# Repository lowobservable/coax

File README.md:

# coax

Tools for connecting to real [IBM 3270](https://en.wikipedia.org/wiki/IBM_3270) type terminals.

## Documentation

* [protocol](protocol/protocol.md) - Protocol documentation

## Hardware

* [interface1](interface1) - Legacy interface using obsolete National Semiconductor DP8340 and DP8341
* [interface2](interface2) - Modern interface using a Lattice iCE40 FPGA and STM32 microcontroller

## Software

* [pycoax](pycoax) - Python interface library

## See Also

* [oec](https://github.com/lowobservable/oec) - IBM 3270 terminal controller (a replacement for the IBM 3174)

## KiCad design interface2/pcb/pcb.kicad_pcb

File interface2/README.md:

# interface2

Modern interface using a Lattice iCE40 FPGA and STM32 microcontroller.

## Hardware

You can find a [complete BOM](https://octopart.com/bom-tool/S80JaI18) on Octopart.

You can find the Gerber files for fabricating a PCB in the [fabrication](pcb/fabrication) directory. I have used JLCPCB to make the PCBs.

## FPGA

For now, the FPGA bitstream must be built using Lattice iCEcube2.

```
cd fpga
make
```

Uses FIFO module from [Sylvain Munaut](https://github.com/smunaut).

## Firmware

The firmware currently provides the ability to send commands and receive responses - it is designed to implement a terminal controller, not a terminal.

You will need [PlatformIO](https://platformio.org/) to build and upload the firmware, only Platform IO Core (the CLI) is required.

Before building the firmware, you will need to generate the FPGA bitstream; see the steps above.

To build and upload the firmware using USB DFU:

```
cd firmware
platformio run -t upload
```

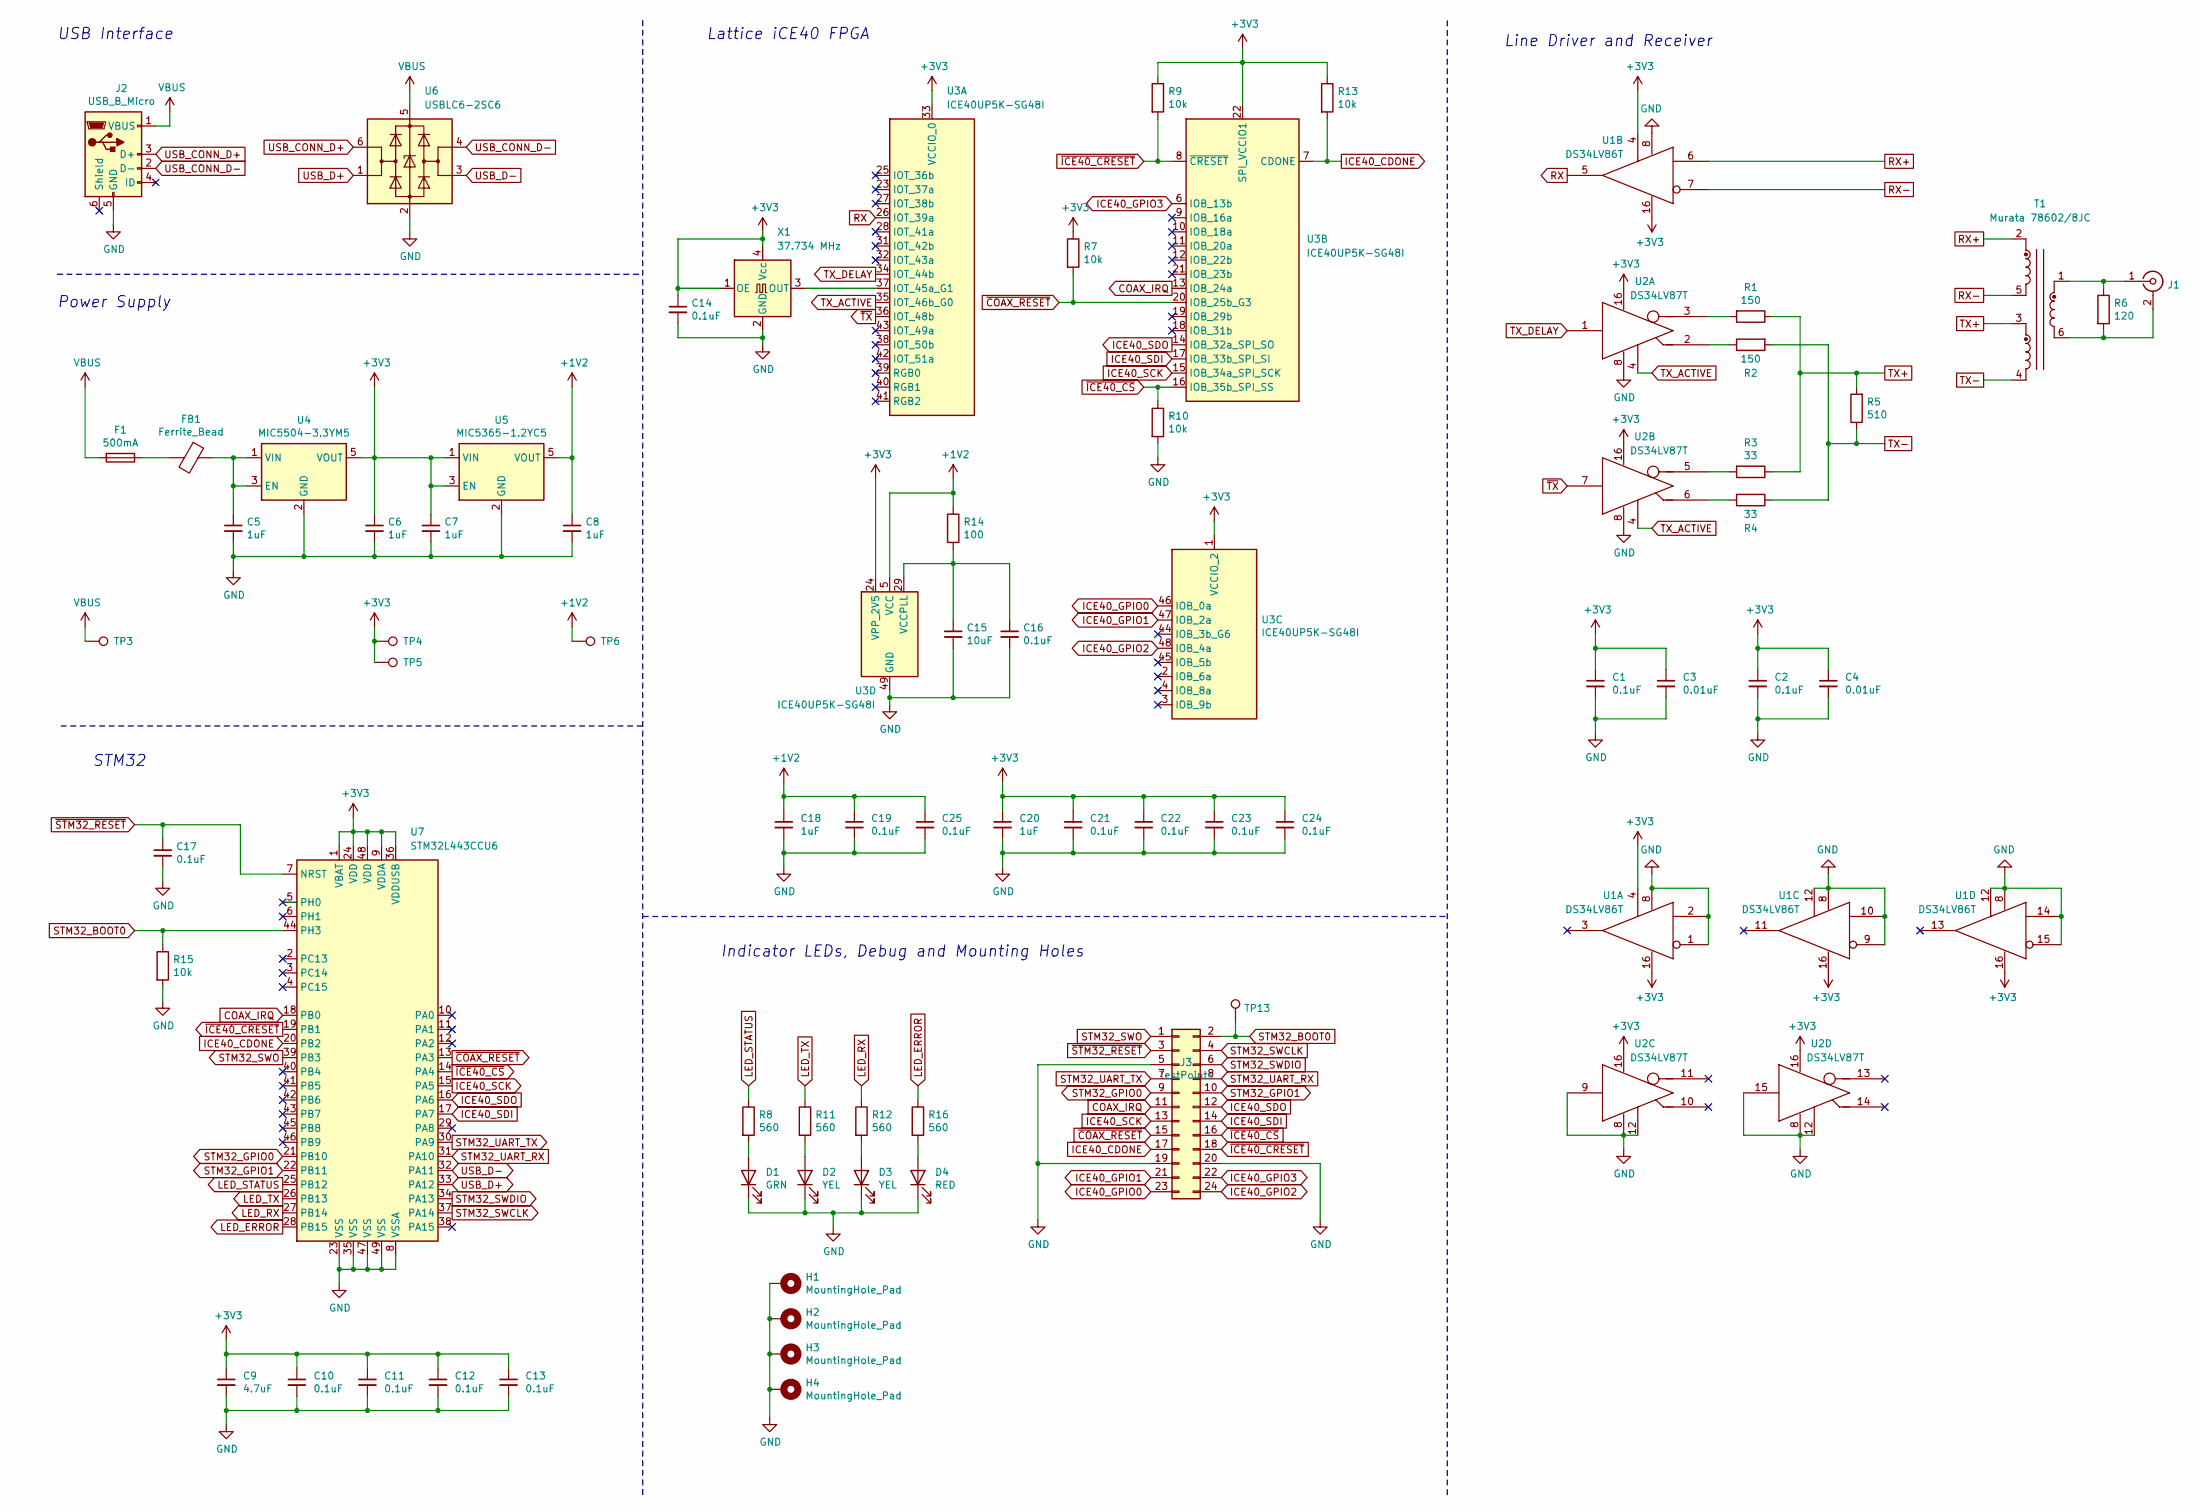
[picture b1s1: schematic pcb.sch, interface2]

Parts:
C1, C2, C10, C11, C12, C13, C14, C16, C17, C19, C21, C22, C23, C24, C25: 0.1uF; C_0603_1608Metric; Part EMK107B7104KA-T
C3, C4: 0.01uF; C_0603_1608Metric; Part HMK107B7103KA-T
C5, C6, C7, C8, C18, C20: 1uF; C_0603_1608Metric; Part EMK107B7105KA-T
C9: 4.7uF; C_0603_1608Metric; Part JMK107BB7475KA-T
C15: 10uF; C_0603_1608Metric; Part JMK107ABJ106KA-T
D1: GRN; LED_0603_1608Metric; Part 150060VS55040
D2, D3: YEL; LED_0603_1608Metric; Part 150060YS55040
D4: RED; LED_0603_1608Metric; Part 150060RS55040
F1: 500mA; Fuse_1206_3216Metric; Part ERB-RG0R50V
FB1: Ferrite_Bead; Fuse_1206_3216Metric; Part CZP2BPTTE101P
H1, H2, H3, H4: MountingHole_Pad; MountingHole_2.7mm_M2.5_ISO7380_Pad
J1: Conn_Coaxial; BNC_Amphenol_B6252HB-NPP3G-50_Horizontal; Part 1-1337543-0
J2: USB_B_Micro; USB_Micro-B_Amphenol_10103594-0001LF_Horizontal; Part 10103594-0001LF
J3: TestPoints; TestPoint_Pad_2x12_D1.0mm
R1, R2: 150; R_0603_1608Metric; Part RCS0603150RFKEA
R3, R4: 33; R_0603_1608Metric; Part RCS060333R0FKEA
R5: 510; R_0603_1608Metric; Part RCS0603510RFKEA
R6: 120; R_0603_1608Metric; Part RCS0603120RFKEA
R7, R9, R10, R13, R15: 10k; R_0603_1608Metric; Part RCS060310K0FKEA
R8, R11, R12, R16: 560; R_0603_1608Metric; Part RCS0603560RFKEA
R14: 100; R_0603_1608Metric; Part RCS0603100RFKEA
T1: Murata 78602/8JC; Murata_786J; Part 78602/8JC
TP3, TP4, TP5, TP6, TP13: TestPoint; TestPoint_Pad_D1.0mm
U1: DS34LV86T; SOIC-16_3.9x9.9mm_P1.27mm; Part DS34LV86T
U2: DS34LV87T; SOIC-16_3.9x9.9mm_P1.27mm; Part DS34LV87T
U3: ICE40UP5K-SG48I; QFN-48-1EP_7x7mm_P0.5mm_EP5.6x5.6mm; Part ICE40UP5K-SG48I
U4: MIC5504-3.3YM5; SOT-23-5; Part MIC5504-3.3YM5-T5
U5: MIC5365-1.2YC5; SOT-353_SC-70-5; Part MIC5365-1.2YC5-TR
U6: USBLC6-2SC6; SOT-23-6; Part USBLC6-2SC6
U7: STM32L443CCU6; QFN-48-1EP_7x7mm_P0.5mm_EP5.6x5.6mm; Part STM32L443CCU6
X1: 37.734 MHz; CDFN3225-4LD-PL-1; Part DSC6001CI2A

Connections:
+1V2: C8.1, C18.1, C19.1, C25.1, R14.1, TP6.1, U3.5 (VCC), U3.30 (VCC), U5.5 (VOUT)
+3V3: C1.1, C2.1, C3.1, C4.1, C6.1, C7.1, C9.1, C10.1, C11.1, C12.1, C13.1, C14.1, C20.1, C21.1, C22.1, C23.1, C24.1, R7.1, R9.1, R13.1, TP4.1, TP5.1, U1.4 (ENABLE), U1.16 (VCC), U2.16 (VCC), U3.1 (VCCIO_2), U3.22 (SPI_VCCIO1), U3.24 (VPP_2V5), U3.33 (VCCIO_0), U4.5 (VOUT), U5.1 (VIN), U5.3 (EN), U7.1 (VBAT), U7.9 (VDDA), U7.24 (VDD), U7.36 (VDDUSB), U7.48 (VDD), X1.1 (OE), X1.4 (Vcc)
COAX_IRQ: J3.11, U3.13 (IOB_24a), U7.18 (PB0)
GND: C1.2, C2.2, C3.2, C4.2, C5.2, C6.2, C7.2, C8.2, C9.2, C10.2, C11.2, C12.2, C13.2, C14.2, C15.2, C16.2, C17.2, C18.2, C19.2, C20.2, C21.2, C22.2, C23.2, C24.2, C25.2, D1.1 (K), D2.1 (K), D3.1 (K), D4.1 (K), H1.1, H2.1, H3.1, H4.1, J2.5 (GND), J3.5, J3.19, J3.20, R10.2, R15.2, U1.1 (E-), U1.2 (E+), U1.8 (GND), U1.9 (E-), U1.10 (E+), U1.12 (ENABLE), U1.14 (E+), U1.15 (E-), U2.8 (GND), U2.9 (INPUT), U2.12 (ENABLE), U2.15 (INPUT), U3.49 (GND), U4.2 (GND), U5.2 (GND), U6.2 (GND), U7.8 (VSSA), U7.23 (VSS), U7.35 (VSS), U7.47 (VSS), U7.49 (VSS), X1.2 (GND)
ICE40_CDONE: J3.17, R13.2, U3.7 (CDONE), U7.20 (PB2)
ICE40_GPIO0: J3.23, U3.46 (IOB_0a)
ICE40_GPIO1: J3.21, U3.47 (IOB_2a)
ICE40_GPIO2: J3.24, U3.48 (IOB_4a)
ICE40_GPIO3: J3.22, U3.6 (IOB_13b)
ICE40_SCK: J3.13, U3.15 (IOB_34a_SPI_SCK), U7.15 (PA5)
ICE40_SDI: J3.14, U3.17 (IOB_33b_SPI_SI), U7.17 (PA7)
ICE40_SDO: J3.12, U3.14 (IOB_32a_SPI_SO), U7.16 (PA6)
LED_ERROR: R16.1, U7.28 (PB15)
LED_RX: R12.1, U7.27 (PB14)
LED_STATUS: R8.1, U7.25 (PB12)
LED_TX: R11.1, U7.26 (PB13)
unnamed: C5.1, FB1.1, U4.1 (VIN), U4.3 (EN)
unnamed: C15.1, C16.1, R14.2, U3.29 (VCCPLL)
unnamed: D1.2 (A), R8.2
unnamed: D2.2 (A), R11.2
unnamed: D3.2 (A), R12.2
unnamed: D4.2 (A), R16.2
unnamed: F1.1, FB1.2
unnamed: J1.1 (In), R6.1, T1.1
unnamed: J1.2 (Ext), R6.2, T1.6
unnamed: R1.2, U2.3 (OUT-)
unnamed: R2.1, U2.2 (OUT+)
unnamed: R3.2, U2.5 (OUT-)
unnamed: R4.2, U2.6 (OUT+)
unnamed: U3.37 (IOT_45a_G1), X1.3 (OUT)
RX: U1.5 (OUT), U3.26 (IOT_39a)
RX+: T1.2, U1.6 (E+)
RX-: T1.5, U1.7 (E-)
STM32_BOOT0: J3.2, R15.1, TP13.1, U7.44 (PH3)
STM32_GPIO0: J3.9, U7.21 (PB10)
STM32_GPIO1: J3.10, U7.22 (PB11)
STM32_SWCLK: J3.4, U7.37 (PA14)
STM32_SWDIO: J3.6, U7.34 (PA13)
STM32_SWO: J3.1, U7.39 (PB3)
STM32_UART_RX: J3.8, U7.31 (PA10)
STM32_UART_TX: J3.7, U7.30 (PA9)
TX+: R1.1, R3.1, R5.2, T1.3
TX-: R2.2, R4.1, R5.1, T1.4
TX_ACTIVE: U2.4 (ENABLE), U3.35 (IOT_46b_G0)
TX_DELAY: U2.1 (INPUT), U3.34 (IOT_44b)
USB_CONN_D+: J2.3 (D+), U6.6 (I/O1)
USB_CONN_D-: J2.2 (D-), U6.4 (I/O2)
USB_D+: U6.1 (I/O1), U7.33 (PA12)
USB_D-: U6.3 (I/O2), U7.32 (PA11)
VBUS: F1.2, J2.1 (VBUS), TP3.1, U6.5 (VBUS)
~COAX_RESET: J3.15, R7.2, U3.20 (IOB_25b_G3), U7.13 (PA3)
~ICE40_CRESET: J3.18, R9.2, U3.8 (~CRESET), U7.19 (PB1)
~ICE40_CS: J3.16, R10.1, U3.16 (IOB_35b_SPI_SS), U7.14 (PA4)
~STM32_RESET: C17.1, J3.3, U7.7 (NRST)
~TX: U2.7 (INPUT), U3.36 (IOT_48b)

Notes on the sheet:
Line Driver and Receiver
Power Supply
USB Interface
Indicator LEDs, Debug and Mounting Holes
STM32
Lattice iCE40 FPGA

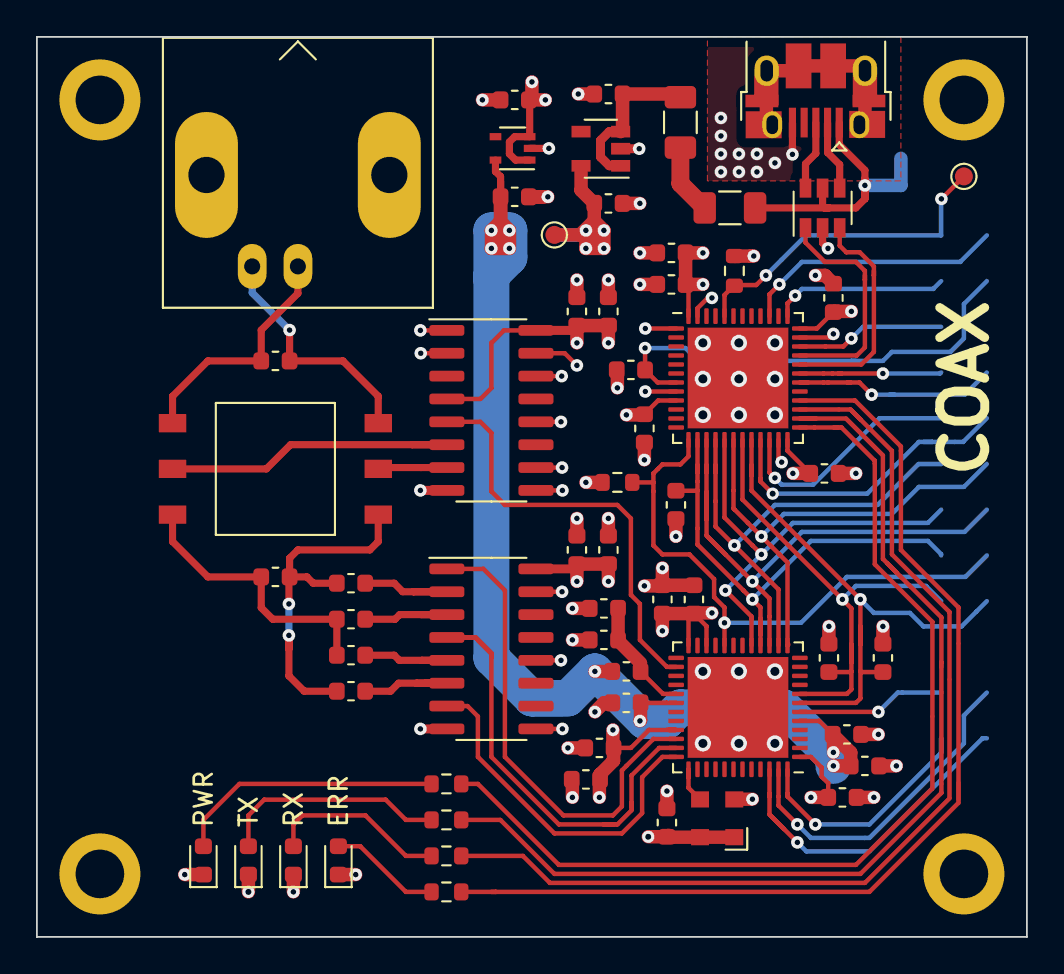
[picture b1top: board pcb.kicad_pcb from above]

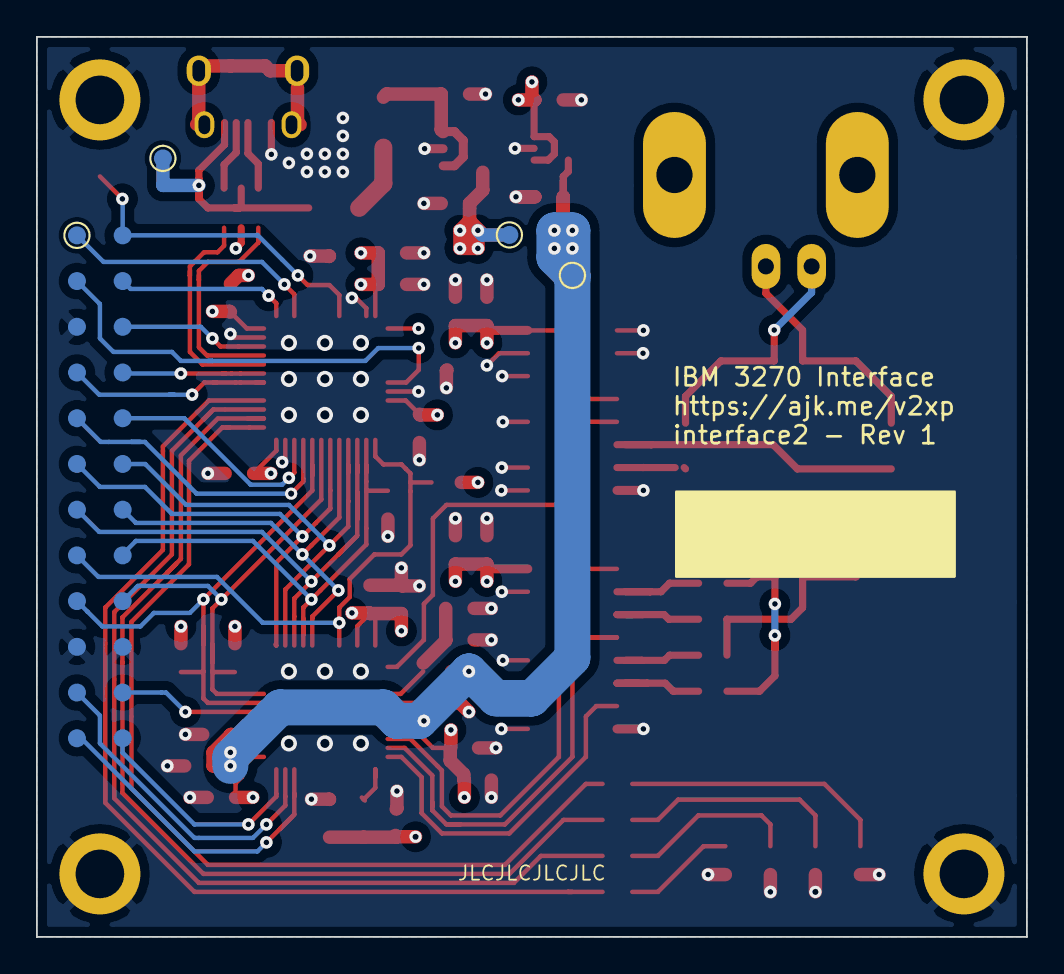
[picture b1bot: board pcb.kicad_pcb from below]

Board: 4 copper layers, 55.0 x 50.0 mm, 68 parts (4 on the bottom side), 55 nets.

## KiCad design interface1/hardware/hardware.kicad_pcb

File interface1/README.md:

# interface1

Legacy interface using obsolete National Semiconductor DP8340 and DP8341.

This project uses several obsolete components; you may be able to find these as _new old stock_. See [interface2](../interface2) for a modern alternative using a Lattice iCE40 FPGA and STM32 microcontroller.

## Hardware

This interface requires an [Arduino Mega 2560 R3](https://store.arduino.cc/usa/mega-2560-r3).

You can find a [complete BOM](https://octopart.com/bom-tool/SZ3rSPgD) on Octopart. I have purchased all current components from Mouser and obsolete ones from eBay.

You can find the Gerber files for fabricating a PCB in the [fabrication](hardware/fabrication) directory. I have used JLCPCB to make the PCBs.

## Firmware

The firmware currently provides the ability to send commands and receive responses - it is designed to implement a terminal controller, not a terminal.

You will need [PlatformIO](https://platformio.org/) to build and upload the firmware, only Platform IO Core (the CLI) is required.

To build and upload the firmware for an Arduino Mega 2560 R3:

```
platformio run -t upload -e mega2560
```

For an original Arduino Mega:

```
platformio run -t upload -e mega1280
```

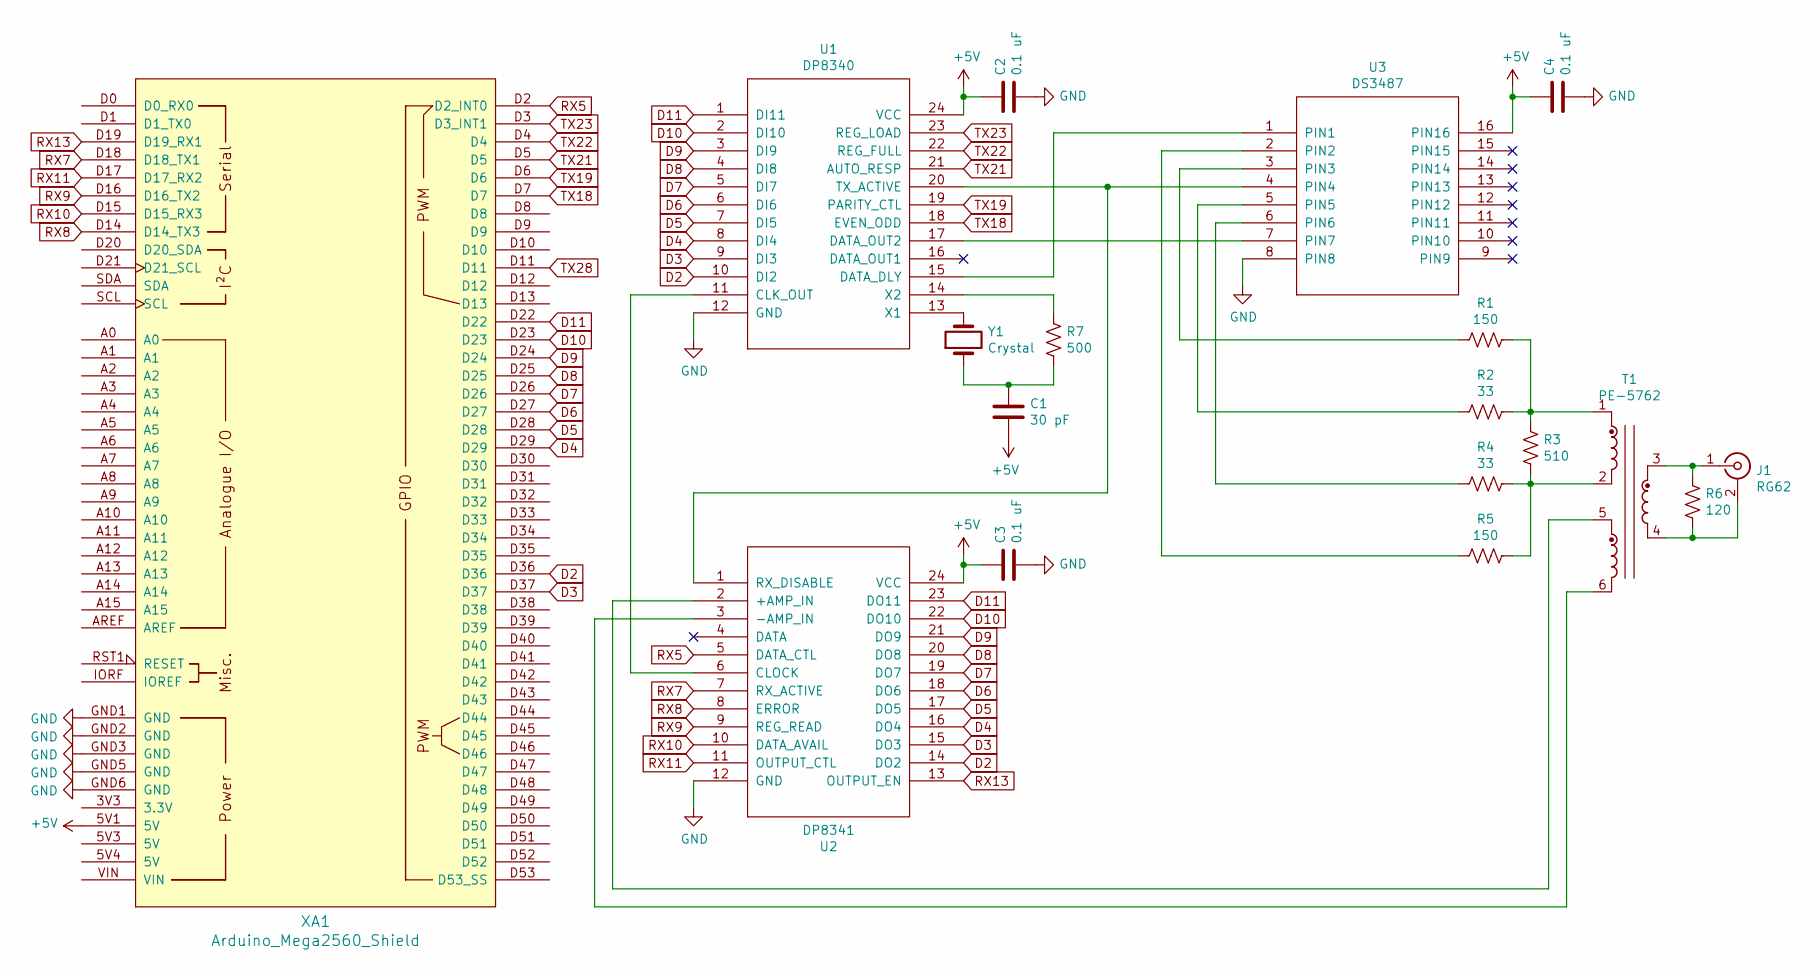
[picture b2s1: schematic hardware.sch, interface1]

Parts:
C1: 30 pF; C_Disc_D9.0mm_W5.0mm_P7.50mm
C2, C3, C4: 0.1 uF; C_Disc_D5.0mm_W2.5mm_P2.50mm
J1: RG62; BNC_Amphenol_B6252HB-NPP3G-50_Horizontal
R1, R5: 150; R_Axial_DIN0207_L6.3mm_D2.5mm_P7.62mm_Horizontal
R2, R4: 33; R_Axial_DIN0207_L6.3mm_D2.5mm_P7.62mm_Horizontal
R3: 510; R_Axial_DIN0207_L6.3mm_D2.5mm_P7.62mm_Horizontal
R6: 120; R_Axial_DIN0207_L6.3mm_D2.5mm_P7.62mm_Horizontal
R7: 500; R_Axial_DIN0207_L6.3mm_D2.5mm_P7.62mm_Horizontal
T1: PE-5762; PE_TH6
U1: DP8340; DIP-24_W15.24mm_Socket
U2: DP8341; DIP-24_W15.24mm_Socket
U3: DS3487; DIP-16_W7.62mm
XA1: Arduino_Mega2560_Shield
Y1: Crystal; Crystal_SMD_HC49-SD

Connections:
+5V: C1.2, C2.1, C3.1, C4.1, U1.24 (VCC), U2.24 (VCC), U3.16 (PIN16), XA1.5V1 (5V)
D2: U1.10 (DI2), U2.14 (DO2), XA1.D36
D3: U1.9 (DI3), U2.15 (DO3), XA1.D37
D4: U1.8 (DI4), U2.16 (DO4), XA1.D29
D5: U1.7 (DI5), U2.17 (DO5), XA1.D28
D6: U1.6 (DI6), U2.18 (DO6), XA1.D27
D7: U1.5 (DI7), U2.19 (DO7), XA1.D26
D8: U1.4 (DI8), U2.20 (DO8), XA1.D25
D9: U1.3 (DI9), U2.21 (DO9), XA1.D24
D10: U1.2 (DI10), U2.22 (DO10), XA1.D23
D11: U1.1 (DI11), U2.23 (DO11), XA1.D22
GND: C2.2, C3.2, C4.2, U1.12 (GND), U2.12 (GND), U3.8 (PIN8), XA1.GND1 (GND), XA1.GND2 (GND), XA1.GND3 (GND), XA1.GND5 (GND), XA1.GND6 (GND)
unnamed: C1.1, R7.2, Y1.1
unnamed: J1.1 (In), R6.1, T1.3
unnamed: J1.2 (Ext), R6.2, T1.4
unnamed: R1.1, U3.3 (PIN3)
unnamed: R1.2, R2.2, R3.1, T1.1
unnamed: R2.1, U3.5 (PIN5)
unnamed: R3.2, R4.2, R5.2, T1.2
unnamed: R4.1, U3.6 (PIN6)
unnamed: R5.1, U3.2 (PIN2)
unnamed: R7.1, U1.14 (X2)
unnamed: T1.5, U2.2 (+AMP_IN)
unnamed: T1.6, U2.3 (-AMP_IN)
unnamed: U1.11 (CLK_OUT), U2.6 (CLOCK)
unnamed: U1.13 (X1), Y1.2
unnamed: U1.15 (DATA_DLY), U3.1 (PIN1)
unnamed: U1.17 (DATA_OUT2), U3.7 (PIN7)
unnamed: U1.20 (TX_ACTIVE), U2.1 (RX_DISABLE), U3.4 (PIN4)
RX5: U2.5 (DATA_CTL), XA1.D2 (D2_INT0)
RX7: U2.7 (RX_ACTIVE), XA1.D18 (D18_TX1)
RX8: U2.8 (ERROR), XA1.D14 (D14_TX3)
RX9: U2.9 (REG_READ), XA1.D16 (D16_TX2)
RX10: U2.10 (DATA_AVAIL), XA1.D15 (D15_RX3)
RX11: U2.11 (OUTPUT_CTL), XA1.D17 (D17_RX2)
RX13: U2.13 (OUTPUT_EN), XA1.D19 (D19_RX1)
TX18: U1.18 (EVEN_ODD), XA1.D7
TX19: U1.19 (PARITY_CTL), XA1.D6
TX21: U1.21 (AUTO_RESP), XA1.D5
TX22: U1.22 (REG_FULL), XA1.D4
TX23: U1.23 (REG_LOAD), XA1.D3 (D3_INT1)

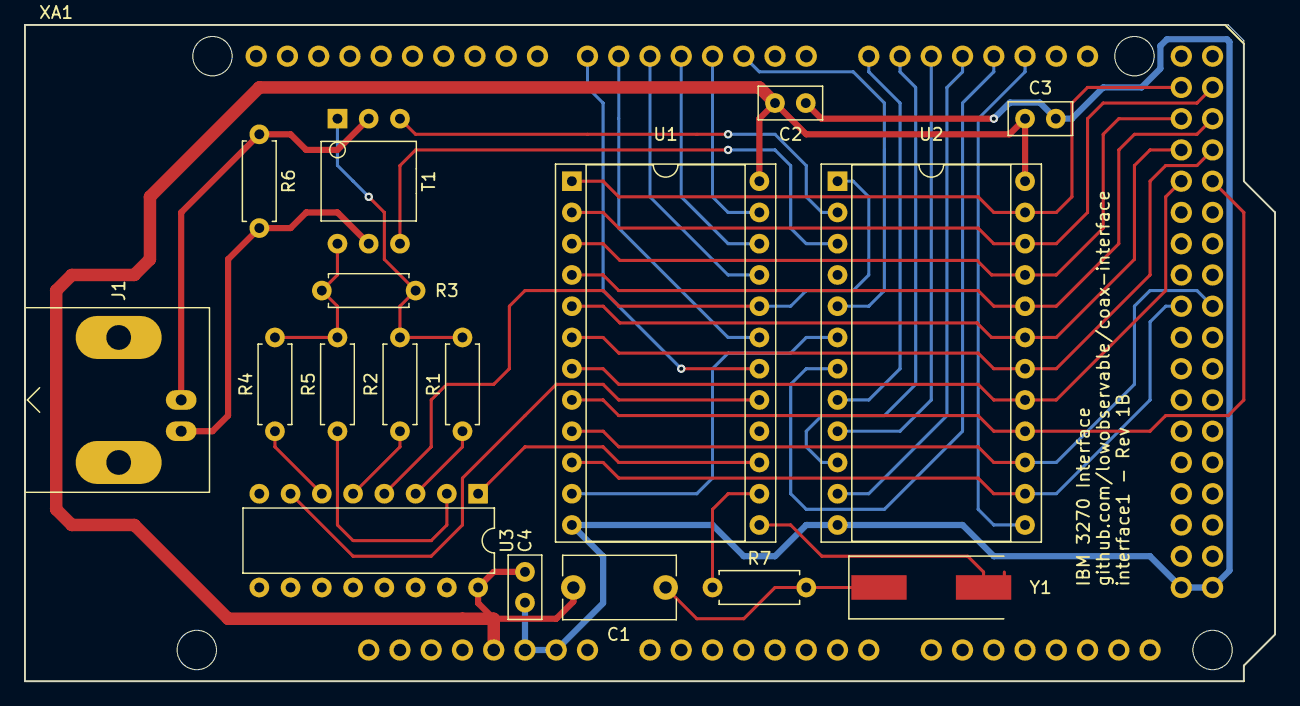
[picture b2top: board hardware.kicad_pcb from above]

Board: 2 copper layers, 101.6 x 53.3 mm, 18 parts (0 on the bottom side), 41 nets.

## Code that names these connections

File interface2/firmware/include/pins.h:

// Copyright (c) 2020, Andrew Kay
//
// Permission to use, copy, modify, and/or distribute this software for any
// purpose with or without fee is hereby granted, provided that the above
// copyright notice and this permission notice appear in all copies.
//
// THE SOFTWARE IS PROVIDED "AS IS" AND THE AUTHOR DISCLAIMS ALL WARRANTIES
// WITH REGARD TO THIS SOFTWARE INCLUDING ALL IMPLIED WARRANTIES OF
// MERCHANTABILITY AND FITNESS. IN NO EVENT SHALL THE AUTHOR BE LIABLE FOR
// ANY SPECIAL, DIRECT, INDIRECT, OR CONSEQUENTIAL DAMAGES OR ANY DAMAGES
// WHATSOEVER RESULTING FROM LOSS OF USE, DATA OR PROFITS, WHETHER IN AN
// ACTION OF CONTRACT, NEGLIGENCE OR OTHER TORTIOUS ACTION, ARISING OUT OF
// OR IN CONNECTION WITH THE USE OR PERFORMANCE OF THIS SOFTWARE.

#pragma once

#include "stm32l4xx_ll_gpio.h"

#define COAX_RESET_Pin GPIO_PIN_3
#define COAX_RESET_GPIO_Port GPIOA
#define COAX_IRQ_Pin GPIO_PIN_0
#define COAX_IRQ_GPIO_Port GPIOB
#define COAX_IRQ_EXTI_IRQn EXTI0_IRQn

#define ICE40_CS_Pin GPIO_PIN_4
#define ICE40_CS_GPIO_Port GPIOA
#define ICE40_SCK_Pin GPIO_PIN_5
#define ICE40_SCK_GPIO_Port GPIOA
#define ICE40_SDO_Pin GPIO_PIN_6
#define ICE40_SDO_GPIO_Port GPIOA
#define ICE40_SDI_Pin GPIO_PIN_7
#define ICE40_SDI_GPIO_Port GPIOA
#define ICE40_CRESET_Pin GPIO_PIN_1
#define ICE40_CRESET_GPIO_Port GPIOB
#define ICE40_CDONE_Pin GPIO_PIN_2
#define ICE40_CDONE_GPIO_Port GPIOB

#define GPIO0_Pin GPIO_PIN_10
#define GPIO0_GPIO_Port GPIOB
#define GPIO1_Pin GPIO_PIN_11
#define GPIO1_GPIO_Port GPIOB

#define LED_STATUS_Pin GPIO_PIN_12
#define LED_STATUS_GPIO_Port GPIOB
#define LED_TX_Pin GPIO_PIN_13
#define LED_TX_GPIO_Port GPIOB
#define LED_RX_Pin GPIO_PIN_14
#define LED_RX_GPIO_Port GPIOB
#define LED_ERROR_Pin GPIO_PIN_15
#define LED_ERROR_GPIO_Port GPIOB

#define USB_D__Pin GPIO_PIN_11
#define USB_D__GPIO_Port GPIOA
#define USB_D_A12_Pin GPIO_PIN_12
#define USB_D_A12_GPIO_Port GPIOA

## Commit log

2019-06-27 More flexible _execute_read_command
2019-06-27 Allow TR/TA response to READ_EXTENDED_ID command
2019-06-27 pycoax 0.1.1
2019-07-06 Fix issue where keyword arguments were not passed to interface
2019-07-06 pycoax 0.1.2
2019-09-06 Adding character map example
2019-10-10 Update interface1 schematic and PCB
2019-12-18 Fix terminal model mapping
2019-12-18 Do not check parity when unpacking data words
2019-12-19 Implemented READ_STATUS
2019-12-21 Refactor execute to take command word
2019-12-21 Add POLL action
2019-12-22 Implement LOAD_CONTROL_REGISTER
2019-12-22 Implement READ_DATA
2019-12-22 Implement LOAD_SECONDARY_CONTROL
2019-12-22 Implement READ_MULTIPLE
2019-12-24 Implement RESET
2019-12-24 Implement LOAD_MASK, SEARCH_FORWARD and SEARCH_BACKWARD
2019-12-24 Implement INSERT_BYTE
2019-12-24 Implement CLEAR
2019-12-25 Add build pycoax action
2019-12-25 pycoax 0.2.0
2020-02-05 Verilog templating
2020-02-08 Adding a 19 MHz clock
2020-02-09 Quiesce pattern
2020-02-09 Code violation and sync bit
2020-02-09 Data
2020-02-09 Parity bit
2020-02-09 Cleanup clocks
2020-02-09 End sequence
2020-02-11 Remove BIT_ALIGN state and improve active
2020-02-11 Adding tx_delay
2020-02-11 Adding tx_inverted and updating pins
2020-02-11 Cleanup
2020-02-13 Initial attempts at multiple word transmission
2020-02-13 Hello world
2020-02-14 Add tx_delay size comment
2020-02-14 Parameterize tx_delay_buffer size
2020-02-14 Clean up full and data loading
2020-02-15 Bit timer module
2020-02-15 Clean up bit timer
2020-02-18 Initial attempt at receiver
2020-02-18 Add data, data_available and data_read
2020-02-22 Attempt DP8340 and DP8341 shims
2020-02-28 Prototype PCB
2020-02-28 Added part numbers
2020-02-29 PCB fabrication
2020-03-04 Drop shims, for now
2020-03-13 Make word packing functions public
2020-03-13 Drop address from command packing functions
2020-03-14 Add TX to top
2020-03-14 Add data word packing functions
2020-03-24 New serial protocol
2020-03-24 Update documentation
2020-03-24 pycoax 0.3.0
2020-03-24 Fix firmware data expansion bug
2020-03-26 Implement receiver error
2020-03-26 pycoax 0.3.1
2020-03-28 Use PlatformIO for firmware
2020-03-28 Fix duplicate import from merge
2020-03-28 Add receiver enable
2020-03-28 Add serial port environment variable to examples
2020-05-12 Add terminal type to TerminalId (CUT and DFT)
2020-05-12 Improve exception messages
2020-05-12 sliplib 0.5.0
2020-05-12 pycoax 0.4.0
2020-05-26 Improve pycoax character map example
2020-05-26 Update pycoax documentation
2020-05-26 Initial protocol documentation
2020-06-12 Update PlatformIO configuration for original Arduino Mega (ATmega1280)
2020-06-12 Add description to invalid message errors
2020-06-12 pycoax 0.4.1
2020-06-14 Start over
2020-06-16 Initial coax_rx_bit_timer
2020-06-21 testing rx_coax_bit_timer on TinyFPGA
2020-06-30 Fix serial data corruption on Windows with Arduino Mega 2560 Rev 3
2020-06-30 pycoax 0.4.2
2020-07-04 some progress...
2020-07-05 Work in progress
2020-07-05 More work in progress
2020-07-05 First hardware test of coax_rx, increase clk frequency
2020-07-05 Add data bus
2020-07-05 Cleanup, maybe, state_counter
2020-07-05 Cleanup internal_data name
2020-07-05 Implement read
2020-07-07 register active and error
2020-07-07 Firmware update...
2020-07-08 Consistency
2020-07-08 Add coax_tx_bit_timer
2020-07-09 Add initial coax_tx
2020-07-09 Integrate coax_tx into top
2020-07-09 Add distortion
2020-07-09 Disable receiver input when not enabled
2020-07-09 Bridge the old and the new
2020-07-09 Headers
2020-07-11 Fix receiver start and end sequence detection
2020-07-11 Teensy is fast, get rid of some premature optimization
2020-07-19 EAB feature
2020-07-19 pycoax 0.5.0
2020-07-20 Faster turnaround time... 3278-2 is too quick
2020-07-20 Make data bus setMode a little more efficient
2020-07-31 Fix bug in TX start sequence generation
2020-08-01 Update development board PCB
2020-08-24 Update pin assignments for new development board
2020-08-26 hacking
2020-08-26 stress test
2020-08-26 discoverer
2020-08-26 forgot msgpack
2020-08-26 Improve analyze.py
2020-09-02 wip - before breaking up dev board
2021-02-07 pyserial 3.5, sliplib 0.6.2
2021-02-07 pycoax 0.5.1
2021-02-09 Fix bug where error template was modified resulting in incorrect message
2021-02-14 Remove unimplemented transmit and receive commands
2021-02-15 pycoax 0.6.0
2021-03-11 Support new interface reset response
2021-03-11 pycoax 0.7.0
2021-03-11 Correct pycoax example in documentation
2021-03-29 Add interface2
2021-05-03 Fix EAB load mask command
2021-05-03 pycoax 0.7.1
2021-05-13 Add jumbo write split option
2021-05-13 pycoax 0.8.0
2021-05-18 hacking about
2021-05-18 actually print some of the data
2021-05-18 something for the new CSVs
2021-05-19 uh, just use stdin for both
2021-05-19 actually, this is cleaner
2021-05-19 maybe, something like this - untested
2021-06-25 Add open_serial_interface function
2021-06-25 Add DFU tool
2021-06-25 pycoax 0.9.0
2021-10-03 Update iCEcube2 makefile for CI
2021-10-04 Update GitHub Actions workflows
2021-10-08 Add FPGA tests to interface2 build workflow
2021-10-08 Add CI infrastructure
2021-10-16 New pycoax API
2021-10-19 Fix bug in handling unsupported READ_EXTERNAL_ID
2021-10-20 Prefer auto spec and spy where possible in unit tests
2021-10-20 Refactor base interface for easier testing
2021-10-21 Return protocol errors when executing multiple commands, don't throw
2021-10-23 Lint pycoax
2021-10-23 pycoax 0.10.0
2021-10-24 More robust coax_rx start sequence detection
2021-10-30 New coax_tx_rx_frontend and coax_rx_blanker modules
2021-11-06 Add 3299 protocol support to interface2
2021-11-06 Drop old pycoax API compatibility
2021-11-12 pycoax 0.11.0
2021-11-30 Fix error handling when getting interface features
2021-11-30 pycoax 0.11.1
2022-02-12 Improve run_tests.sh script
2022-02-19 Add SNOOPIE module
2022-02-19 Don't run SNOOPIE report on ReceiveTimeout
2023-01-14 Ignore pyserial port configuration error on Windows
2023-01-14 pycoax 0.11.2
2023-08-02 Refactor serial interface _pack_transmit_receive_message
2023-08-26 GitHub Actions maintenance
2024-09-03 Bump actions/download-artifact from 3 to 4.1.7 in /.github/workflows
    Bumps [actions/download-artifact](https://github.com/actions/download-artifact) from 3 to 4.1.7.
    - [Release notes](https://github.com/actions/download-artifact/releases)
    - [Commits](https://github.com/actions/download-artifact/compare/v3...v4.1.7)
    ---
    updated-dependencies:
    - dependency-name: actions/download-artifact
2024-10-08 Best practice to not include versions in setup.py install_requires
2026-02-08 attempt to read all features
